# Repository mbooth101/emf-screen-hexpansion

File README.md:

# Screen Hexpansion

More screens is more better. Plug-in an auxialliary screen or two to maximise the amount of data you can display at a time! Or use them to create a multiocular Tildagon, just like everyone's favourite unicode glyph, the [multiocular O](https://en.wikipedia.org/wiki/Cyrillic_O_variants#Multiocular_O) "ꙮ".

## Firmware Install/Update

### Over-The-Air

You can initialise (and subsequently update) the Screen Hexpansion's firmware using the Tildagon badge's built-in "Hexpansions" app. Select the port it's plugged into and enter the VID `0x4D42` and PID `0x5EE5` to get the correct firmware.

### Manually

If you need to manually re-flash the Hexpansion firmware for any reason, or you want to install custom firmware, you can do so by inserting the Screen Hexpansion into port 2 of your Tildagon, and running the following commands:

```
cd emf-screen-hexpansion
mpremote mount EEPROM + run EEPROM/prepare_eeprom.py + cp EEPROM/app.py :/hexpansion/app.py
```

Once complete, the Screen Hexpansion may be inserted into any port. The script is just hard-coded to port 2 for flashing the firmware.

## License

This repo is MIT licensed and CERN Open Hardware licensed.

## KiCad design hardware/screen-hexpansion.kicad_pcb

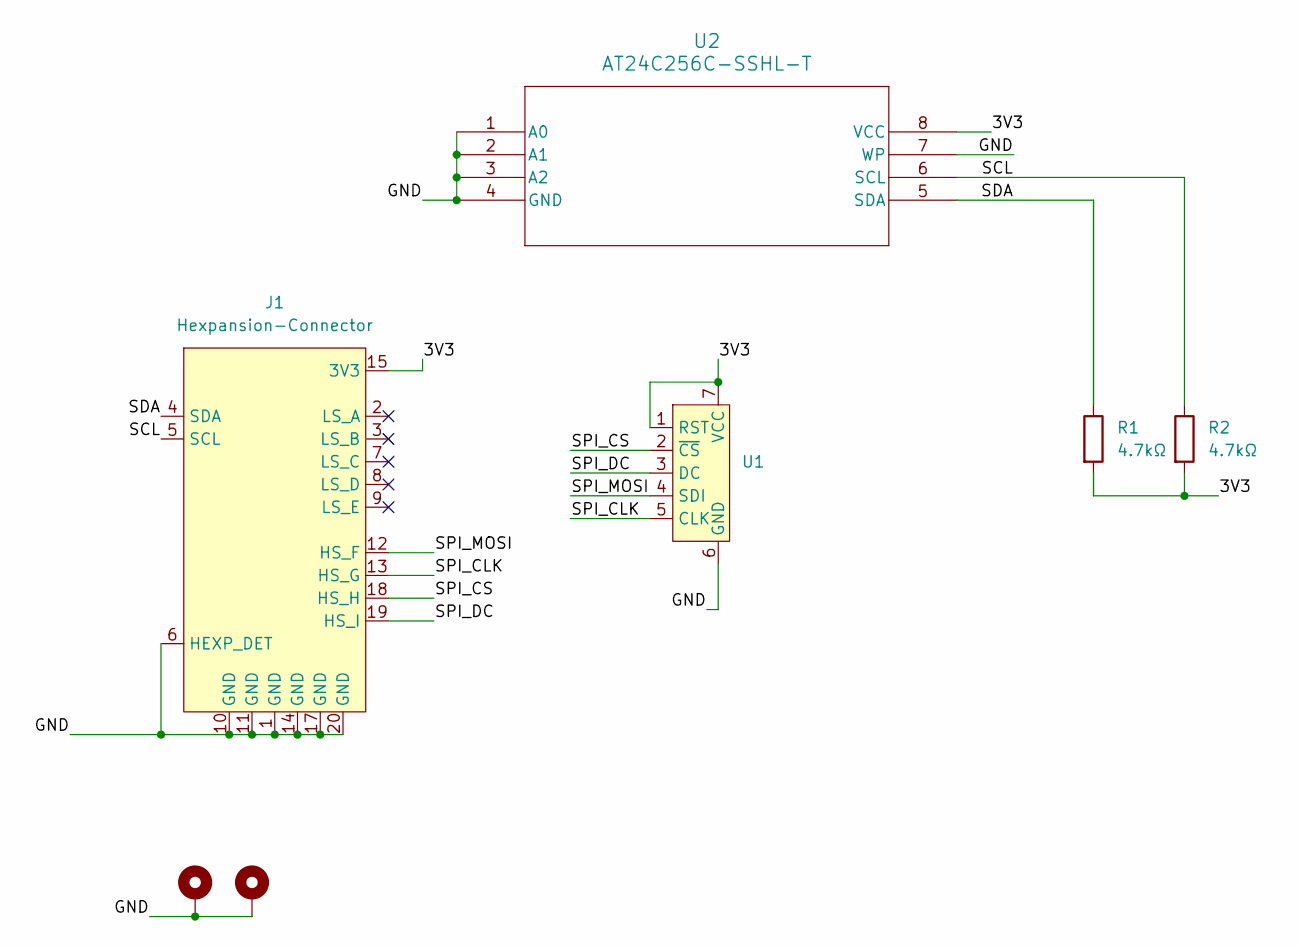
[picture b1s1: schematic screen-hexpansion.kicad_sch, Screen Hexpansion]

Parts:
H1, H2: MountingHole_Pad; MountingHole_2.2mm_M2_Pad_Via
J1: Hexpansion-Connector; hexpansion-edge-connector
R1, R2: 4.7kΩ; R_0603_1608Metric
U1: PinHeader_1x07_P2.54mm_Vertical_LockPads
U2: AT24C256C-SSHL-T; SOIC-8_3.9x4.9mm_P1.27mm

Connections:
/3V3: J1.15 (3V3), J1.16 (3V3), R1.2, R2.2, U1.1 (RST), U1.7 (VCC), U2.8 (VCC)
/GND: H1.1, H2.1, J1.1 (GND), J1.6 (HEXP_DET), J1.10 (GND), J1.11 (GND), J1.14 (GND), J1.17 (GND), J1.20 (GND), U1.6 (GND), U2.1 (A0), U2.2 (A1), U2.3 (A2), U2.4 (GND), U2.7 (WP)
/SCL: J1.5 (SCL), R2.1, U2.6 (SCL)
/SDA: J1.4 (SDA), R1.1, U2.5 (SDA)
/SPI_CLK: J1.13 (HS_G), U1.5 (CLK)
/SPI_CS: J1.18 (HS_H), U1.2 (~CS)
/SPI_DC: J1.19 (HS_I), U1.3 (DC)
/SPI_MOSI: J1.12 (HS_F), U1.4 (SDI)

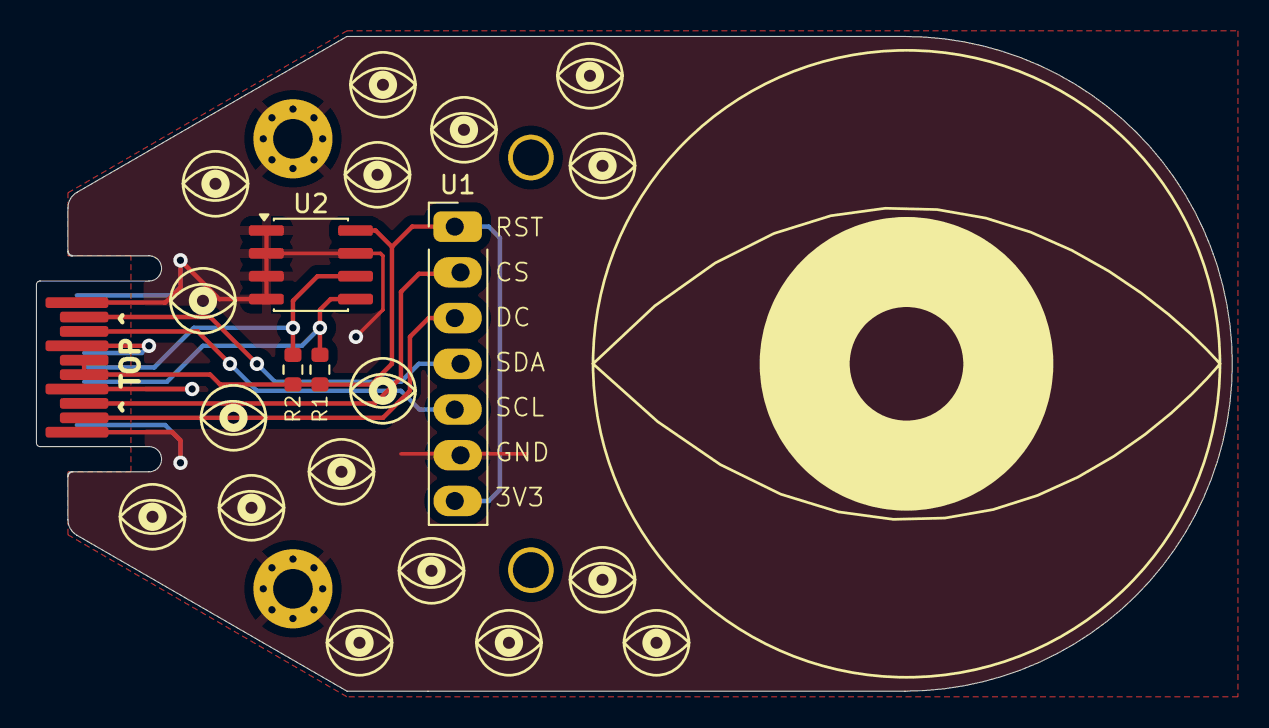
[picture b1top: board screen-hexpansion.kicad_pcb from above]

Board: 2 copper layers, 66.4 x 36.3 mm, 7 parts (0 on the bottom side), 8 nets.

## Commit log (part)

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2026-06-19 Initial commit of v1 Screen Hexpansion
2026-06-19 Add PCB production files
2026-06-27 Add datasheets for screen and eeprom components
2026-06-30 Simple app to test the functionality of the hexpansion
